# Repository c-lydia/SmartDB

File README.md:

# SmartDB

SmartDB is a household electrical fault detection and protection system spanning ESP32
firmware, KiCad hardware, a device-ingestion gateway, API examples, and engineering
reference material.

## Project links

| Project | Hosted website | GitHub | Role |
|---|---|---|---|
| SmartDB | [Documentation](https://smartdb-docs.vercel.app) | [c-lydia/SmartDB](https://github.com/c-lydia/SmartDB) | Hardware, firmware, backend/API and engineering documentation |
| SmartDB documentation | [Current architecture](https://smartdb-docs.vercel.app/system/architecture.html) · [PCB downloads](https://smartdb-docs.vercel.app/hardware/index.html#files-and-previews) · [API/team handoff](https://smartdb-docs.vercel.app/system/index.html) | [Documentation sources](https://github.com/c-lydia/SmartDB/tree/main/docs) | Public documentation site |
| ByteLab | [ByteLab Web](https://bytelab-web.vercel.app) | [c-lydia/ByteLab](https://github.com/c-lydia/ByteLab) | Related firmware development workspace; desktop and browser editions |
| SmartDB user dashboard | Not published yet | Repository not available yet | Owned by the frontend team; links will be added when available |

ByteLab is a development companion, not SmartDB's user dashboard. The optional local
SmartDB developer console is for API testing and is not publicly deployed.

## Repository map

| Path | Contents |
|---|---|
| [`backend/`](backend/) | Python CoAP/CBOR ingestion gateway and tests |
| [`cloud/`](cloud/README.md) | Implemented Firebase HTTP API, emulator launcher and frontend integration guide |
| [`dashboard/`](dashboard/README.md) | Optional developer console; user dashboard belongs to the frontend team |
| [`esp_idf/smartdb_fusion/`](esp_idf/smartdb_fusion/README.md) | PlatformIO ESP-IDF v2 system firmware and separate ESP32-CAM firmware; build/flash guide |
| [`smart_db/`](smart_db/smart_db.kicad_pro) | Earlier KiCad design and historical manufacturing outputs |
| [`smart_db_v2/`](smart_db_v2/README.md) | Selected hardware revision; review findings and ESP32-S3 module decision |
| [`postman/`](postman/documents/README.md) | User-facing HTTP API requests, OpenAPI contract, and collection guide |
| [`docs/`](docs/) | System architecture and engineering references |

## Run the backend locally

Run `sh system.sh` from this folder (Node.js 22 LTS and Java 21+ required). It starts
Firebase emulators and the optional developer console, prints a local administrator login,
and preserves local data on clean shutdown. The API is at `http://127.0.0.1:5000/api/v1`.
See the [team API handoff](cloud/README.md) for integration, Postman, device provisioning,
configuration commands and deployment. The frontend team owns the user dashboard.

## Set up the two boards

The [web documentation source](docs/index.md) includes the setup guide, hardware notes,
API guide and architecture. Rebuild it with `./docs/build.sh` and open
`docs/_build/html/index.html`; see [website maintenance](docs/README.md).

Open `esp_idf/smartdb_fusion` as the VS Code project folder, then choose
**Terminal → Run Task → SmartDB: Setup**. Alternatively, launch the menu from that folder:

```sh
./setup.sh
```

Choose **1** to enter Wi-Fi settings, **2** to set up the ESP32-CAM, then **3** to set up
the SmartDB main board. The menu selects ports, offers the initial firmware flash, saves
settings and checks Wi-Fi. Use **4** for protection limits. Later connection changes are
saved over USB without rebuilding. The camera and main board each need their own firmware;
PlatformIO combines their source files automatically.

Connect each board directly to the computer for setup. The main board's J6 camera socket
supplies power only and cannot program the camera. See the [firmware guide](esp_idf/smartdb_fusion/README.md)
for connections, configuration, recovery and calibration. The [full architecture](docs/architecture_full_v1.1.md)
separates implemented bench behavior from production requirements; the [backend guide](backend/README.md)
covers the separate CoAP ingestion gateway.

## Current hardware

SmartDB v2 is being corrected for an ESP32-S3-WROOM-1-N16R8 module supplied and assembled
by JLCPCB. The existing ESP32-WROOM-32 development board is separate test hardware, not
the selected PCB module. The module replacement is applied in the KiCad
schematic and PCB, with corrected reset/boot wiring and an updated [pin map](smart_db_v2/pinmap.csv).
The current revision targets a **low-voltage bench load**, with corrected 5 V logic power,
USB, CT input and a separate normally-open relay contact connector. The permanent
[v2 project](smart_db_v2/smart_db/smart_db.kicad_pro) now contains the 95 × 78 mm
compact redesign with an AP63203 buck supply, four copper layers, and the SmartDB
logo and connector labels. All PCB connections are routed, with wider signal and power
traces and continuous inner ground planes. ERC, DRC, connectivity and schematic parity
checks report zero issues. See the [v2 review](smart_db_v2/README.md) for current validation results,
previews and the archived previous board. It is not a mains protection board.

## Project maturity

The v2 bench firmware now covers SCT-013 **isolated low-voltage AC** monitoring, MLX90640
thermal sensing, local relay protection with physical re-arm, persistent configuration/events,
registered RGB–thermal fusion and optional HTTPS diagnostic telemetry using the Postman
contract. Build `smartdb_s3` for the main board and `esp32cam` for the separate camera.
See the [firmware guide](esp_idf/smartdb_fusion/README.md) for configuration, flashing,
calibration and implementation limits. Source/build verification is complete; physical bench
validation remains pending. The PCB logic supply is DC; the CT measurement is AC-only.

This is an engineering-stage repository, not a production-certified safety device. The
backend's secure transport integration and several firmware/hardware validation activities
remain explicit pre-production work. Do not use it as the sole protective mechanism for a
live electrical installation.

## Code style

Maintained application code uses two-space indentation for JavaScript, CSS, and shell,
four spaces for Python and C, and a 100-column target. Prettier handles the web/API code,
Ruff formats and checks Python, clang-format handles the current firmware, and shfmt
formats shell scripts. Editor defaults are in `.editorconfig`.

C code uses an open, Python-like layout: one statement per line, spaces around operators,
braced control-flow blocks, and blank lines between functions and logical steps.

Install the development tools with `npm ci` and, inside a Python virtual environment,
`python -m pip install -r requirements-dev.txt`. Install clang-format and shfmt separately;
the formatting baseline uses clang-format 23.1.0 and shfmt 3.13.1.

```sh
npm run format        # Apply formatting
npm run format:check  # Check formatting and Python imports/errors without rewriting files
npm run build        # Build the developer console
npm test             # Run the cloud API tests using local Firebase emulators
python -m pytest backend/tests
sh esp_idf/smartdb_fusion/tools/check.sh
```

The formatting commands cover `backend`, `cloud`, `dashboard`, documentation support
scripts/styles, launchers, and first-party code in `esp_idf/smartdb_fusion`. They exclude
generated outputs, local firmware configuration, upstream sensor drivers, legacy firmware
examples, hardware design files, archives, and Postman exports.

## Related projects

- [ByteLab](https://github.com/c-lydia/ByteLab) — firmware development workspace; [hosted browser edition](https://bytelab-web.vercel.app) and [SmartDB integration guide](https://smartdb-docs.vercel.app/related/bytelab.html).

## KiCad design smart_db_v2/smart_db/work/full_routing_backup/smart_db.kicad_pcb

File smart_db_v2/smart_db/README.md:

# SmartDB compact redesign — board routing complete

Updated 2026-10-10. **Fully routed bench prototype; fabrication review remains.**

Open [smart_db.kicad_pro](smart_db.kicad_pro) in KiCad. The editable
[schematic](smart_db.kicad_sch), [PCB](smart_db.kicad_pcb), project-local symbol and
footprint libraries are saved together here. This is the permanent v2 project,
moved from `../compact_wip/`. The previous routed bench revision and its reports
are preserved in [the archive](../archive/bench_before_compact_2026-10-08/README.md).

## Saved work

- Draft 95 × 78 mm four-layer placement, outward-facing connectors and four M3
  mounting holes with screw-head copper clearances.
- Revised AP63203 buck supply, bulk/local decoupling, ADC supply filter and test points.
- Schematic organized into six numbered subsystem boxes.
- Monochrome vector logo extracted from the cover of
  `formal_docs/proposal/SmartDB_proposal_final.pdf`, saved as
  [work/smartdb-logo-monochrome.svg](work/smartdb-logo-monochrome.svg).
  The logo is now on the front silkscreen, together with functional connector,
  BOOT/RESET, status and power labels. The back has connector pin and polarity labels.
- Corrected overlaps involving the relay flyback diode, MCU reset capacitor/pullup,
  ADC decoupling and relay-coil decoupling. The local ESP32 footprint now matches
  the board, including its four-layer antenna keepout and edge silkscreen treatment.

## Connector access and routing

Working board construction: **four-layer FR-4, 1.6 mm overall thickness,
1 oz outer copper and 0.5 oz inner copper**, following the request for standard
construction. The layer order is signal/power–ground–ground–signal/power.
Manufacturer-specific dielectric spacing remains to be selected.

- J3 is the four-pin I²C header. Its pins now project approximately 5.5 mm past
  the left board edge. Front and back labels identify **1 SDA, 2 SCL, 3 GND, 4 3V3**.
  J2 remains the two-pin regulated 5 V screw terminal.
- J4 moved 7.64 mm toward the left edge. Its original mid-mount cutout is retained;
  the unnecessary additional recess is removed. D7 moved 6 mm toward the connector.
- All nets are routed, including buck supply, relay/load, ADC, I²C, UART, USB,
  reset/boot, LEDs and buzzer. Signals remain on F.Cu and B.Cu; both inner layers
  remain ground planes. Final copper contains 608 segments and 88 vias.
- The buck switch and bootstrap connections are short front-layer routes. The
  output has a wider distribution path and separate feedback branch. Load contacts
  use 1 mm traces without vias. Ground stitches connect the ADC, input protection,
  decoupling and MCU regions to the inner planes.
- R13 moved to (73, 70) mm to open a clean reset/enable routing path.
- The USB main pair is manually routed, with 0.2 mm traces, 0.3 mm gap and two
  layer transitions per main path. Preferred widths are now 0.30 mm for signals,
  0.60 mm for power, 0.75 mm for the 5 V/coil supply and 1.00 mm for load contacts.
  Actual routing retains narrower sections in congested channels and pad escapes;
  the minimum is 0.20 mm. USB dimensions were preserved.
- USB appearance now uses a **simplified local visualization**, clearly identified
  in `SmartDB.3dshapes/`. The manufacturer STEP download returned HTTP 403, and
  KiCad's referenced model was unavailable. This is not an enclosure-fit model.

## STEP export

[smart_db.step](smart_db.step) now exports successfully with all three previously
problematic parts included. D6, J1 and J4 reference project-local STEP files through
`${KIPRJMOD}`. J1 uses the [official Same Sky model](https://www.sameskydevices.com/product/resource/3dmodel/sj-3523-smt-tr),
aligned to the footprint. D6 uses a simplified 3.5 × 2.8 × 0.6 mm package preview
based on [ROHM's drawing, page 263](https://fscdn.rohm.com/en/products/databook/catalog/common/shortform2023/SF2023_EN_P247_LEDs.pdf).
J4 uses a STEP solid version of the existing simplified USB preview. D6 and J4
are visual approximations, not certified enclosure-fit models.

Model sources and transforms are recorded in `SmartDB.3dshapes/provenance.json`.
The model fix preserves all copper, pads, placements and rules. Its original CAD
and incomplete STEP are preserved in `work/before_step_model_fix/`.
Reopen the PCB from disk before exporting in an already-open KiCad window;
an old editor buffer still contains the previous model references.

## Two-camera connections

- **J3:** MLX90640 thermal camera, 1 SDA / 2 SCL / 3 GND / 4 3V3.
- **J6:** USB-A **5 V camera power output**, using a
  [TE 292303-7](https://www.te.com/en/product-292303-7.html) socket with SMD
  contacts and two through-hole shell anchors. Connect a short **USB-A to
  micro-USB cable** to the external ESP32-CAM-MB base shown in the reference photo.
  USB pin 1 is +5V, pin 4 and the shell are ground; pins 2 and 3 are intentionally
  unconnected. This is a dedicated camera power connection, with no USB host,
  data, programming or charging-port negotiation on J6.

J6 is at the bottom edge, at (103, 117.3) mm. It branches from F1's
protected output, with a 1.0 mm main trace on B.Cu, a 0.75 mm fuse-pad connection
and paired 0.8/0.4 mm vias at both ends. A 0.75 mm front-layer connection reaches
VBUS without crossing the existing 3.3 V route. C25 (10 µF, 16 V, X7R, 0805) and
C26 (100 nF, 16 V, X7R, 0603) provide local bypassing near J6; capacitor and
connector ground vias join the internal planes. All pre-camera routes and
placements are preserved. The logo was reduced and moved left for clearance.
The local USB-A footprint only moves the three edge-clipped silkscreen segments
to F.Fab; contact pads and the KiCad STEP model are unchanged. TE recommends
1.42 mm PCB thickness for this connector; verify shell retention and soldering
with actual parts on the project's 1.6 mm PCB before fabrication release.
F1's symbol now correctly identifies its specified part as a
one-time fast-acting fuse, rather than a resettable device.

Wi-Fi is the image-data path. The current [PlatformIO ESP-IDF firmware](../../esp_idf/smartdb_fusion/README.md)
has an `esp32cam` target serving authenticated fresh QVGA JPEGs at `/capture`, and a
`smartdb_s3` target combining those images with MLX90640 data. This is request-driven
capture, not a USB video stream. Real alignment and capture timing still need hardware validation.
The older SD-card diagnostic camera project remains separate.

Run the firmware project's `./setup.sh` menu or its **SmartDB: Setup** VS Code task to
install/configure each board. Program the camera by connecting its base directly to the
computer; J6 cannot program it. Configure the camera first so the menu can supply its Wi-Fi
address to the S3. Subsequent Wi-Fi/token/endpoint changes persist in NVS without reflashing;
protection limits are also configurable through the menu, with physical re-arm still required.

Supply both boards through J2 from regulated 5 V; a 2 A capable source is a
provisional supply target. J4 USB-C remains the data/programming connection;
J6 USB-A supplies camera power. The shared 1.5 A F1 is not
an independent camera current limiter. Reserve 0.5 A for the camera/base and target
no more than 1.1 A combined continuous input at 25°C; this is a design budget,
not a measured current rating. Temperature derating, simultaneous Wi-Fi bursts,
camera flash/SD activity, startup and cable voltage drop still need validation.
See [power review and sources](work/camera_power_review.json). The pre-addition
CAD and reports are preserved in `work/before_camera_power/`; the preceding
JST camera-power revision is preserved in `work/before_camera_usb/`.

See [routing review](work/routing_review.md), [copper PDF](work/routing_current.pdf)
and [3D preview](work/connectors_current.png). Existing placement, schematic and
label previews below have also been regenerated.

## Validation status and remaining work

Current KiCad 10.0.6 results: **ERC 0 violations; PCB DRC 0 geometric/library/silkscreen
violations, 0 unconnected items, 0 schematic/PCB mismatches.**
No clearance rules, DRC severities or exclusions were changed. Default and Power
preferred widths changed to 0.30 and 0.60 mm at the user’s request. The resume baseline had 22 placement
violations (including three pad shorts), 113 unconnected items and no parity issues.

Current review outputs:

- [Placement PDF](work/placement_current.pdf) / [PNG](work/placement_current.png)
- [Bottom labels PDF](work/back_labels_current.pdf) / [PNG](work/back_labels_current.png)
- [Schematic PDF](work/schematic_current.pdf) and [netlist](work/netlist_current.xml)
- [ERC](work/erc_current.json), [DRC](work/drc_routing_current.json), and
  [source hashes and checks](work/validation_current.json)

Files without the `current` suffix remain historical intermediate outputs.
`work/resume_backup/` preserves the board, schematic, project and local footprint
as they were at the start of this continuation. `SNAPSHOT.json` describes the
original paused snapshot; it is not the hash manifest for today's revised sources.

Routing is complete. USB impedance and timing still need manufacturer stackup
review and measurement. The selected 1 oz construction does not qualify the
buck circuit for its IC’s maximum 2 A rating; current and thermal limits require review.
Check connector access, mounting clearances, capacitor placement, current paths,
voltage drop, USB geometry, antenna clearance and silkscreen. Recheck labels after
routing and regenerate the review outputs. Verify the exact supply, component selections
and capacitor derating before fabrication. Hardware load-step, brownout, relay,
thermal, USB and ADC-noise measurements remain necessary; a rule-check pass cannot
establish that assembled hardware works.

No enclosure dimensions or J2 supply model have been confirmed.
The design remains scoped to a regulated 5 V supply and a provisional 5–24 V DC,
up-to-1 A resistive relay test load. No mains use.

## Resuming the editing scripts

`work/` preserves the staging scripts and evidence; `work/helpers/` preserves
helpers they import. They contain original absolute `/tmp/smartdb_review/...`
paths and some rebuild earlier stages. **Do not run them blindly against this
snapshot.** Restore the original staging structure or review/update paths first.
The files at this snapshot's root are the authoritative saved CAD state.
`SNAPSHOT.json` records the original paths and hashes of all copied files.

The new `work/resume_placement.py` and `work/add_board_labels.py` resolve paths
relative to this project. The first requires KiCad's Python runtime and refuses
to move components once tracks/vias exist; the second uses ordinary Python and
replaces only its own deterministically identified graphics. In this environment:

```sh
flatpak run --command=python3 org.kicad.KiCad work/resume_placement.py
python3 work/add_board_labels.py
```

These are placement-stage tools. Do not replay placement after hand edits without
reviewing its explicit coordinates. Use `work/validate_current.py` after generating
fresh ERC, DRC and netlist outputs to refresh the source-hash/check manifest.

The connector/routing scripts added in this session are preserved as engineering
work records, not a one-command rebuild pipeline. Some restore earlier board
stages or append copper. **Do not replay them on the current routed board.**
The root CAD files and `work/validation_current.json` are authoritative. The
older `drc_placement_current.json` describes the placement-only milestone.

`work/routed_checkpoint/` preserves the completed CAD and final DRC report.
`work/full_routing_backup/` preserves the earlier partially routed state.
An older editor copy saved during routing is preserved separately in
`work/editor_saved_during_routing.kicad_pcb`. Reopen the project before editing
so an old editor buffer does not overwrite the completed routes.

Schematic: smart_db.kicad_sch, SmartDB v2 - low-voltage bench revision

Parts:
BZ1: Buzzer (3V3 type TBD); Buzzer_12x9.5RM7.6
C1: 220nF; C_0805_2012Metric_Pad1.18x1.45mm_HandSolder
C2, C9: 10uF; C_0805_2012Metric_Pad1.18x1.45mm_HandSolder
C3, C10: 100nF; C_0805_2012Metric_Pad1.18x1.45mm_HandSolder
C4: 10uF 10V X7R; C_0805_2012Metric
C5: 10uF 10V X7R; C_1206_3216Metric
C6, C20: 100nF 10V X7R; C_0805_2012Metric_Pad1.18x1.45mm_HandSolder
C7, C8, C23: 22uF 10V X7R; C_1206_3216Metric
C11: 1uF; C_0805_2012Metric_Pad1.18x1.45mm_HandSolder
C15, C18: 100nF; C_0603_1608Metric
C16, C17: 4.7uF; C_0805_2012Metric_Pad1.18x1.45mm_HandSolder
C19: 10uF 10V X7R; C_0805_2012Metric_Pad1.18x1.45mm_HandSolder
C21: 100nF 25V X7R; C_0603_1608Metric
C22, C24: 100uF 10V; CP_Elec_6.3x7.7
D1: M7 (1N4007 SMD); D_SMA
D2: ADC POWER; LED_0805_2012Metric_Pad1.15x1.40mm_HandSolder
D5: POWER; LED_0805_2012Metric_Pad1.15x1.40mm_HandSolder
D6: SMLVN6RGB1U1; LED_ROHM_SMLVN6
D7: SP0503BAHTG; SOT-143
D8: USB BRIDGE POWER; LED_0805_2012Metric_Pad1.15x1.40mm_HandSolder
D9, D10: BAT54S; SOT-23
F1: 046701.5NRHF 1.5A; Fuse_0603_1608Metric
H1, H2, H3, H4: M3 mounting; MountingHole_3.2mm_M3
J1: SCT-013-000 ONLY; Jack_3.5mm_CUI_SJ-3523-SMT_Horizontal
J2: REGULATED 5V INPUT; TerminalBlock_Phoenix_MKDS-1,5-2_1x02_P5.00mm_Horizontal
J3: THERMAL_I2C; PinHeader_1x04_P2.54mm_Horizontal_Edge
J4: USB_C_Receptacle_USB2.0_14P; USB_C_Receptacle_Amphenol_12401948E412A_Preview
J5: TEST_LOAD; TerminalBlock_Phoenix_MKDS-1,5-2_1x02_P5.00mm_Horizontal
K1: G5LE-1 DC5; Relay_SPDT_Omron-G5LE-1
L1: 6.8uH SRP5030TA-6R8M; L_Bourns_SRP5030T
Q1, Q2: AO3400A; SOT-23
R1, R2: 1k 1%; R_0805_2012Metric_Pad1.20x1.40mm_HandSolder
R3, R4: 10k 1%; R_0805_2012Metric_Pad1.20x1.40mm_HandSolder
R6, R15: 100; R_0805_2012Metric_Pad1.20x1.40mm_HandSolder
R7, R8: 4.7k; R_0805_2012Metric_Pad1.20x1.40mm_HandSolder
R9, R21: 1k; R_0805_2012Metric_Pad1.20x1.40mm_HandSolder
R12, R16, R17, R18, R22: 330; R_0805_2012Metric_Pad1.20x1.40mm_HandSolder
R13, R14: 10k; R_0805_2012Metric_Pad1.20x1.40mm_HandSolder
R19: 22.1k; R_0805_2012Metric_Pad1.20x1.40mm_HandSolder
R20: 47.5k; R_0805_2012Metric_Pad1.20x1.40mm_HandSolder
R23: 18 ohm 1% 0.25W; R_0805_2012Metric_Pad1.20x1.40mm_HandSolder
R24, R25: 5.1k; R_0805_2012Metric_Pad1.20x1.40mm_HandSolder
R26, R27, R28: 100k; R_0805_2012Metric_Pad1.20x1.40mm_HandSolder
R29: 0R 1A min; R_0805_2012Metric
R30: 10R 1%; R_0603_1608Metric
SW2: BOOT; SW_Push_1P1T_NO_CK_KMR2
SW3: RESET; SW_Push_1P1T_NO_CK_KMR2
TP1: LOGIC_5V_FUSED; TestPoint_Pad_D1.5mm
TP2: VCC; TestPoint_Pad_D1.5mm
TP3: MCU_3V3; TestPoint_Pad_D1.5mm
TP4: ADC_3V3; TestPoint_Pad_D1.5mm
TP5: BGND; TestPoint_Pad_D1.5mm
U1: ADS1115IDGS; TSSOP-10_3x3mm_P0.5mm
U3: AP63203WU-7; TSOT-23-6
U4: ESP32-S3-WROOM-1-N16R8; ESP32_S3_WROOM_1_Edge; JLCPCB Part C2913202
U5: CP2102N-A02-GQFN28; QFN-28-1EP_5x5mm_P0.5mm_EP3.35x3.35mm

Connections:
ADC_3V3: C3.1, C4.1, D9.2 (K), D10.2 (K), R3.1, R30.2, TP4.1 (1_1), U1.8 (VDD)
ADC_AIN0: C1.1, D9.3 (COM), R1.2, U1.4 (AIN0)
ADC_AIN1: C1.2, D10.3 (COM), R2.2, U1.5 (AIN1)
ADC_LED_A: D2.2 (A), R9.2
BGND: C2.2, C3.2, C4.2, C5.2, C6.2, C7.2, C8.2, C9.2, C10.2, C11.2, C15.2, C16.2, C17.2, C18.2, C19.2, C20.2, C22.2, C23.2, C24.2, D2.1 (K), D5.1 (K), D6.4 (GK), D6.5 (RK), D6.6 (BK), D7.1 (A), D8.1 (K), D9.1 (A), D10.1 (A), J2.1, J3.3, J4.A1 (GND), J4.A12 (GND), J4.B1 (GND), J4.B12 (GND), J4.SH (SHIELD), Q1.2 (S), Q2.2 (S), R4.2, R20.2, R24.2, R25.2, R26.2, R27.2, R28.2, SW2.1, SW3.1, TP5.1 (1_1), U1.1 (ADDR), U1.3 (GND), U1.6 (AIN2), U1.7 (AIN3), U3.4 (GND), U4.1 (GND), U4.40 (GND), U4.41 (GND), U5.3 (GND), U5.29 (GND)
BOOT: R14.2, SW2.2, U4.27 (IO0)
BUCK_BST: C21.1, U3.6 (BST)
BUCK_SW: C21.2, L1.1, U3.5 (SW)
BUZZER_DRIVE: R15.1, U4.5 (IO5)
BUZZER_LOW: BZ1.2 (-), Q2.3 (D)
CTL: R6.1, R27.1, U4.4 (IO4)
CT_BIAS: C2.1, J1.S, R2.1, R3.2, R4.1, R23.2
CT_HI: J1.T, R1.1, R23.1
EN: C11.1, R13.2, SW3.2, U4.3 (EN)
LED_B: R18.1, U4.12 (IO8)
LED_B_A: D6.1 (BA), R18.2
LED_G: R17.1, U4.7 (IO7)
LED_G_A: D6.3 (GA), R17.2
LED_R: R16.1, U4.6 (IO6)
LED_R_A: D6.2 (RA), R16.2
LOAD_IN: J5.1, K1.1
LOAD_OUT: J5.2, K1.3
LOGIC_5V_FUSED: C5.1, C6.1, C19.1, C20.1, C22.1, C24.1, D1.1 (K), F1.2, K1.5, TP1.1 (1_1), U3.2 (EN), U3.3 (IN)
LOGIC_5V_IN: F1.1, J2.2
MCU_3V3: BZ1.1 (+), C9.1, C10.1, C23.1, J3.4, R7.1, R8.1, R12.1, R13.1, R14.1, R29.2, TP3.1 (1_1), U4.2 (3V3)
unnamed: D5.2 (A), R12.2
unnamed: Q2.1 (G), R15.2, R26.1
RELAY_GATE: Q1.1 (G), R6.2, R28.1
RELAY_LOW: D1.2 (A), K1.2, Q1.3 (D)
RX: U4.37 (TXD0), U5.25 (RXD)
SCL: J3.2, R7.2, U1.10 (SCL), U4.38 (IO2)
SDA: J3.1, R8.2, U1.9 (SDA), U4.18 (IO10)
TX: U4.36 (RXD0), U5.26 (TXD)
USB_CC1: J4.A5 (CC1), R24.1
USB_CC2: J4.B5 (CC2), R25.1
USB_D+: D7.2 (K), J4.A6 (D+), J4.B6 (D+), U5.4 (D+)
USB_D-: D7.3 (K), J4.A7 (D-), J4.B7 (D-), U5.5 (D-)
USB_LED_A: D8.2 (A), R22.2
USB_RESET: R21.2, U5.9 (~RST)
USB_VBUS: D7.4 (K), J4.A4 (VBUS), J4.A9 (VBUS), J4.B4 (VBUS), J4.B9 (VBUS), R19.1
USB_VBUS_SENSE: R19.2, R20.1, U5.8 (VBUS)
VCC: C7.1, C8.1, C15.1, C16.1, C17.1, C18.1, L1.2, R9.1, R21.1, R22.1, R29.1, R30.1, TP2.1 (1_1), U3.1 (FB), U5.6 (VDD), U5.7 (VREGIN)

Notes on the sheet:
01 POWER / 5 V TO 3.3 V
J2 regulated 5 V only. Buck + local reservoirs. Not battery charging.
02 USB / UART PROGRAMMING
USB is data only; J2 powers the board. Hold BOOT, pulse RESET.
03 ESP32-S3 / BOOT / RESET
ESP32-S3-WROOM-1-N16R8. Module RF keepout on every copper layer.
04 CT / ADC ANALOG FRONT END
AC current transformer only. Differential AIN0-AIN1, address 0x48.
05 RELAY / TEST LOAD
Normally-open dry contact loop. 5-24 V DC / 1 A resistive bench target.
06 INDICATORS / EXTERNAL I2C
3.3 V logic only. Buzzer part selection and bench measurements pending.
MECHANICAL + MEASUREMENT POINTS

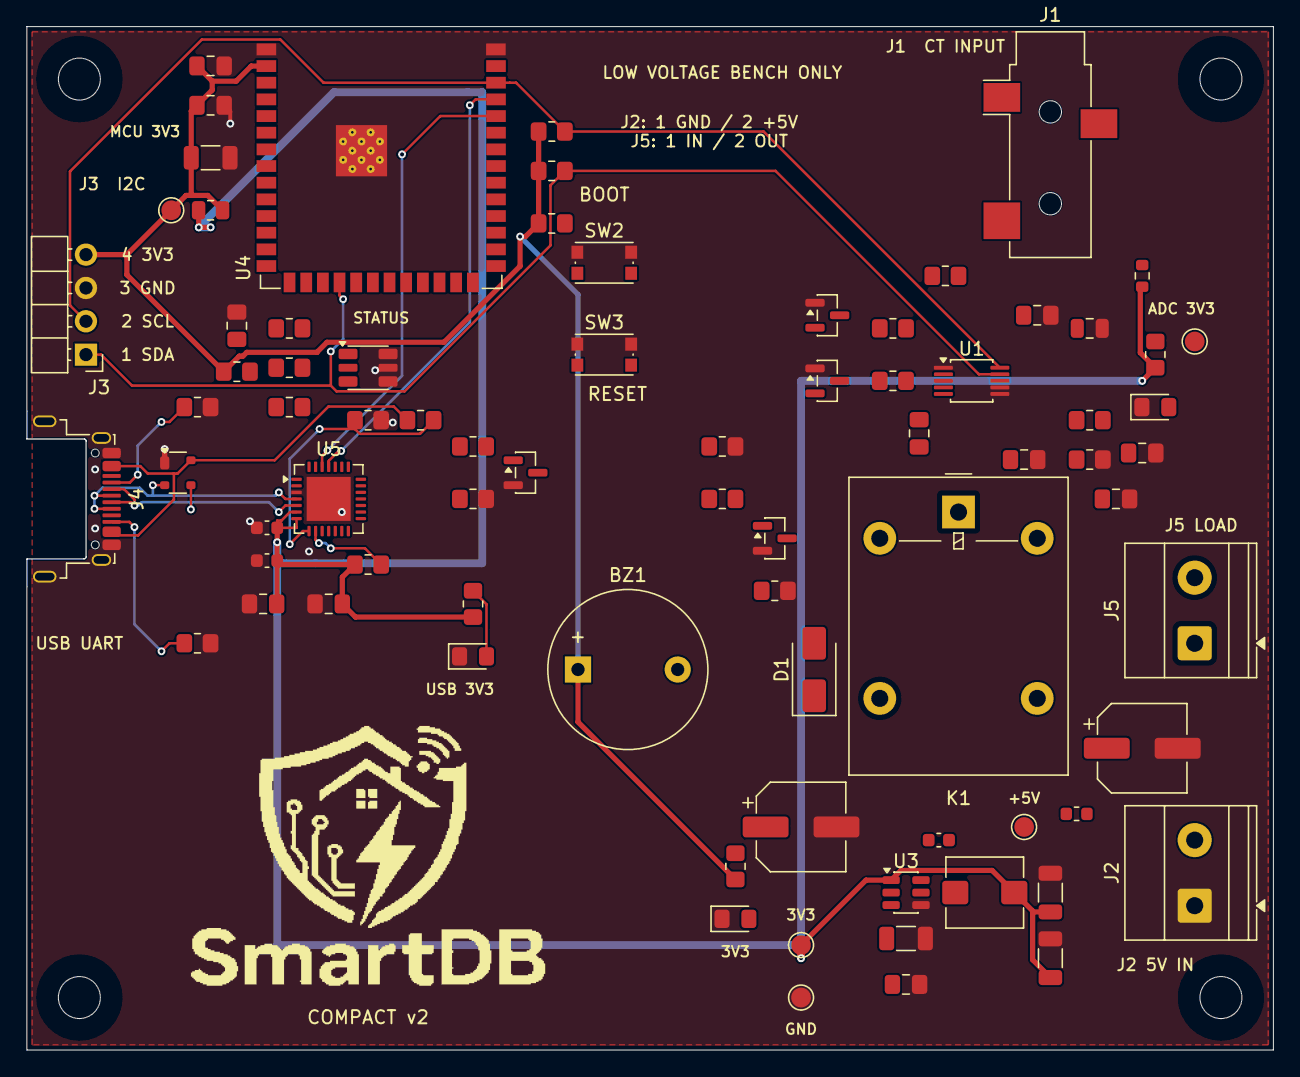
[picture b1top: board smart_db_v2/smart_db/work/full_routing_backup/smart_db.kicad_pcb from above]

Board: 4 copper layers, 95.0 x 78.0 mm, 82 parts (0 on the bottom side), 42 nets.

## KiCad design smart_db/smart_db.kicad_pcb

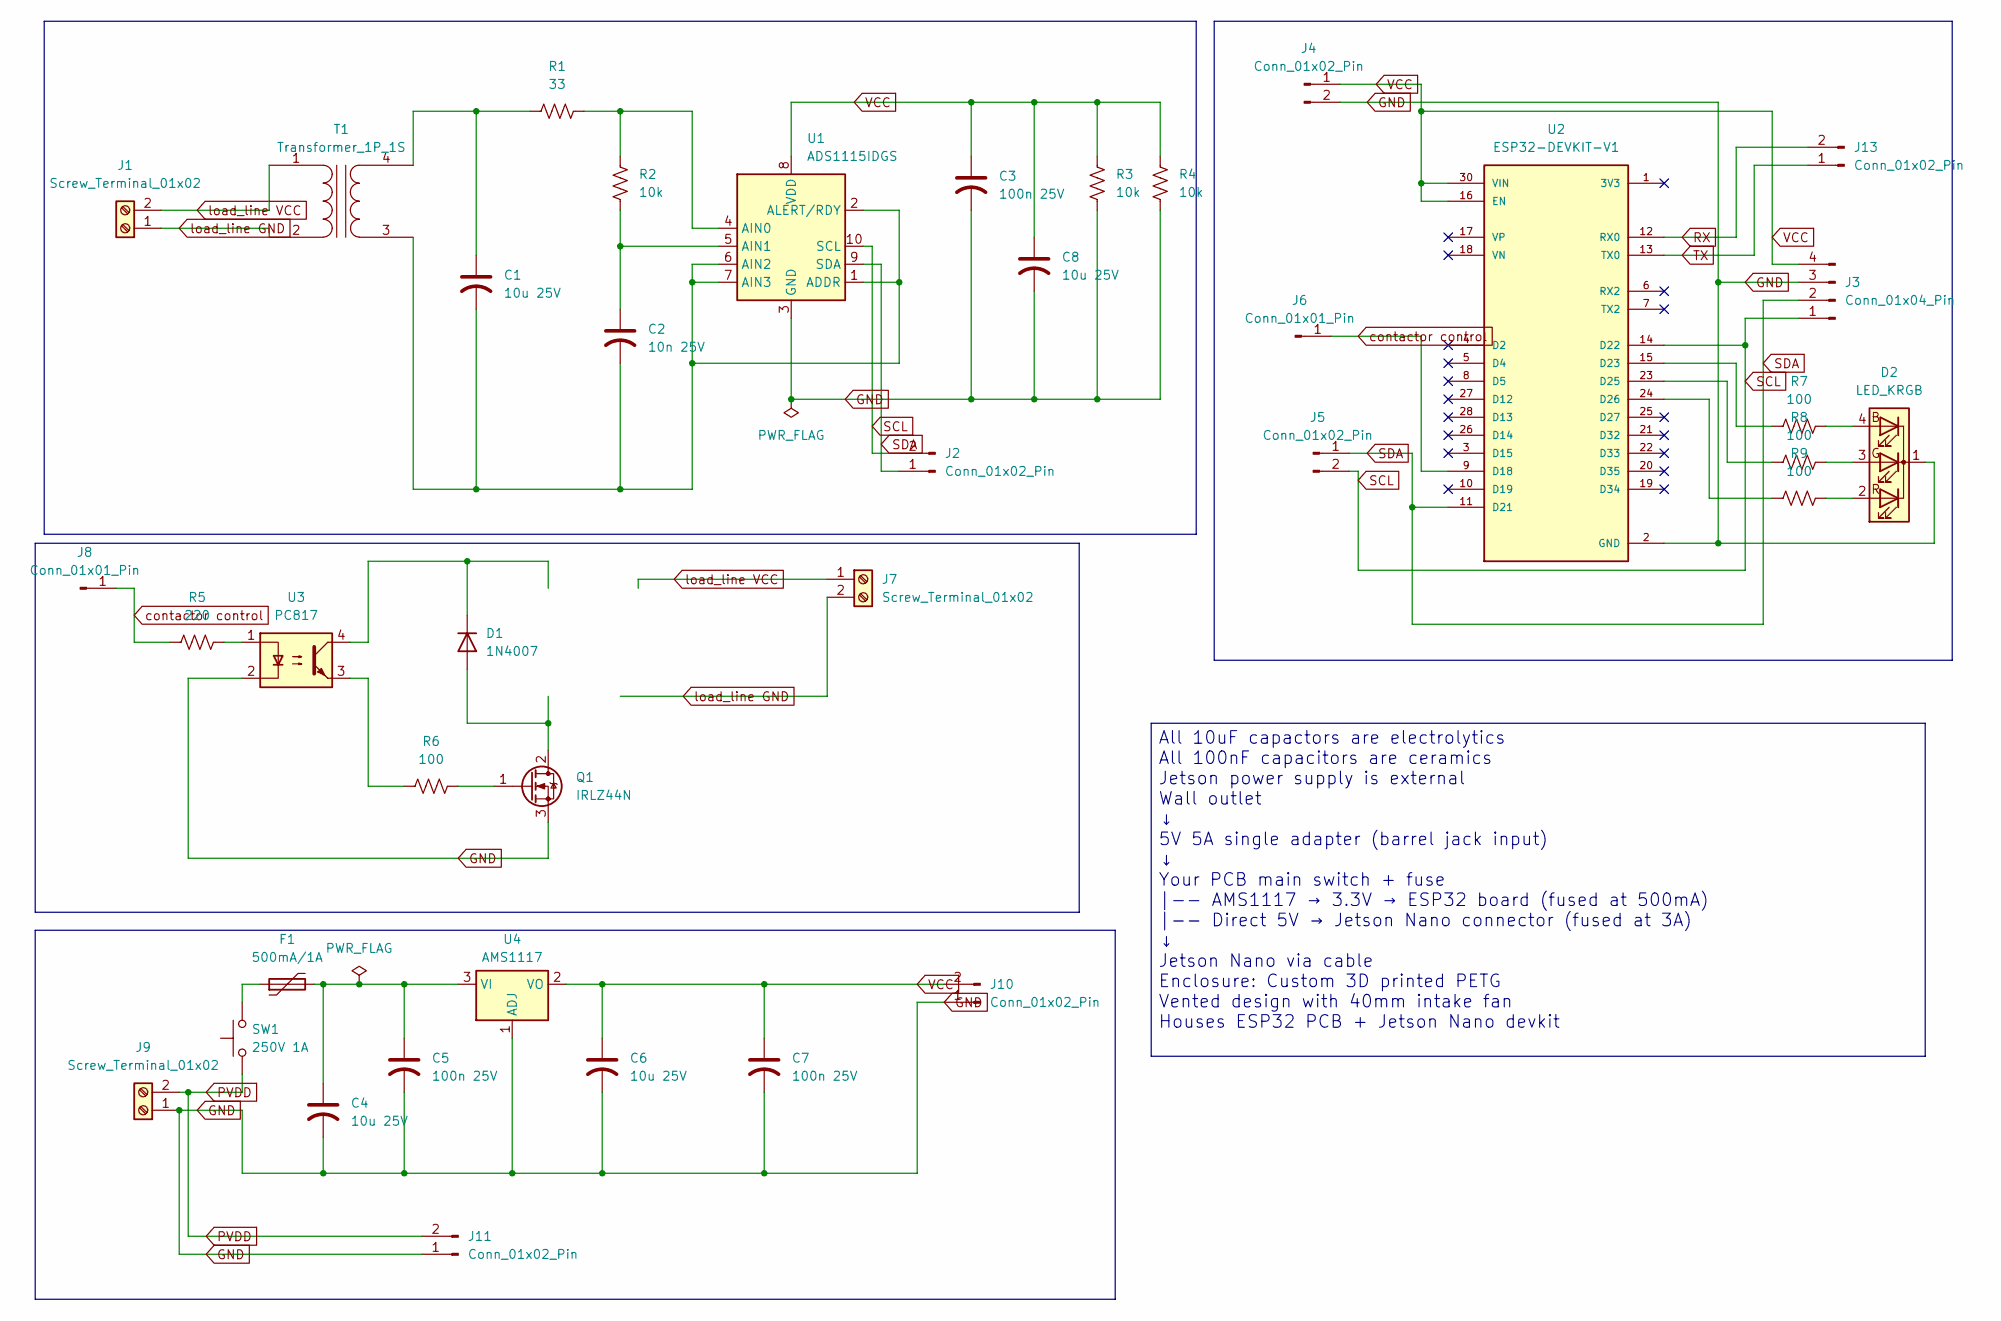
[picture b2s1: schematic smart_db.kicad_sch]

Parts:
C1, C4, C6, C8: 10u 25V; CP_Radial_D5.0mm_P2.50mm
C2: 10n 25V; C_Disc_D3.0mm_W1.6mm_P2.50mm
C3, C5, C7: 100n 25V; C_Disc_D3.0mm_W1.6mm_P2.50mm
D1: 1N4007; D_DO-41_SOD81_P10.16mm_Horizontal
D2: LED_KRGB; LED_D5.0mm-4_RGB
F1: 500mA/1A; Fuse_Bourns_MF-RHT050
J1, J7, J9: Screw_Terminal_01x02; TerminalBlock_RND_205-00276_1x02_P5.00mm_Vertical
J2, J4, J5, J10, J11, J13: Conn_01x02_Pin; PinHeader_1x02_P2.54mm_Vertical
J3: Conn_01x04_Pin; PinHeader_1x04_P2.54mm_Vertical
J6, J8: Conn_01x01_Pin; PinHeader_1x01_P2.54mm_Vertical
Q1: IRLZ44N; TO-220-3_Vertical
R1: 33; R_Axial_DIN0207_L6.3mm_D2.5mm_P10.16mm_Horizontal
R2, R3, R4: 10k; R_Axial_DIN0204_L3.6mm_D1.6mm_P7.62mm_Horizontal
R5: 220; R_Axial_DIN0204_L3.6mm_D1.6mm_P2.54mm_Vertical
R6: 100; R_Axial_DIN0204_L3.6mm_D1.6mm_P2.54mm_Vertical
R7, R8, R9: 100; R_Axial_DIN0204_L3.6mm_D1.6mm_P7.62mm_Horizontal
SW1: 250V 1A; SW_PUSH_1P1T_6x3.5mm_H5.0_APEM_MJTP1250
T1: Transformer_1P_1S; TerminalBlock_RND_205-00278_1x04_P5.00mm_Vertical
U1: ADS1115IDGS; TSSOP-10_3x3mm_P0.5mm
U2: ESP32-DEVKIT-V1; MODULE_ESP32_DEVKIT_V1; PARTREV N/A
U3: PC817; DIP-4_W7.62mm
U4: AMS1117; SOT-223-3_TabPin2

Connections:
GND: C3.2, C4.2, C5.2, C6.2, C7.2, C8.2, D2.1 (K), J3.3, J4.2, J9.1, J10.1, J11.1, Q1.3 (S), R3.2, R4.2, U1.3 (GND), U2.2 (GND), U2.29 (GND), U3.2, U4.1 (ADJ); also elsewhere on the board
unnamed 1: D1.2 (A), Q1.2 (D); also elsewhere on the board
unnamed 2: D1.1 (K), U3.4; also elsewhere on the board
unnamed: D2.4 (BA), R7.2
unnamed: D2.3 (GA), R8.2
unnamed: D2.2 (RA), R9.2
unnamed: F1.1, SW1.2
unnamed: Q1.1 (G), R6.1
unnamed: R5.2, U3.1
unnamed: R6.2, U3.3
unnamed: C1.2, C2.2, T1.3 (SA), U1.1 (ADDR), U1.2 (ALERT/RDY), U1.6 (AIN2), U1.7 (AIN3)
unnamed: C1.1, R1.1, T1.4 (SB)
unnamed: R1.2, R2.1, U1.4 (AIN0)
unnamed: C2.1, R2.2, U1.5 (AIN1)
unnamed: R7.1, U2.15 (D23)
unnamed: R8.1, U2.23 (D25)
unnamed: R9.1, U2.24 (D26)
unnamed: C4.1, C5.1, F1.2, U4.3 (VI)
PVDD: J9.2, J11.2, SW1.1; also elsewhere on the board
RX: J13.2, U2.12 (RX0)
SCL: J2.2, J3.1, J5.2, U1.10 (SCL), U2.14 (D22)
SDA: J2.1, J3.2, J5.1, U1.9 (SDA), U2.11 (D21)
TX: J13.1, U2.13 (TX0)
VCC: C3.1, C6.1, C7.1, C8.1, J3.4, J4.1, J10.2, R3.1, R4.1, U1.8 (VDD), U2.16 (EN), U2.30 (VIN), U4.2 (VO)
contactor control: J6.1 (Pin_1_1), J8.1 (Pin_1_1), R5.1, U2.9 (D18)
load_line GND: J1.1, J7.2, T1.2 (AB); also elsewhere on the board
load_line VCC: J1.2, J7.1, T1.1 (AA); also elsewhere on the board

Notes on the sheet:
All 10uF capactors are electrolytics All 100nF capacitors are ceramics Jetson power supply is external Wall outlet ↓ 5V 5A single adapter (barrel jack input) ↓ Your PCB main switch + fuse |-- AMS1117 → 3.3V → ESP32 board (fused at 500mA) |-- Direct 5V → Jetson Nano connector (fused at 3A) ↓ Jetson 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

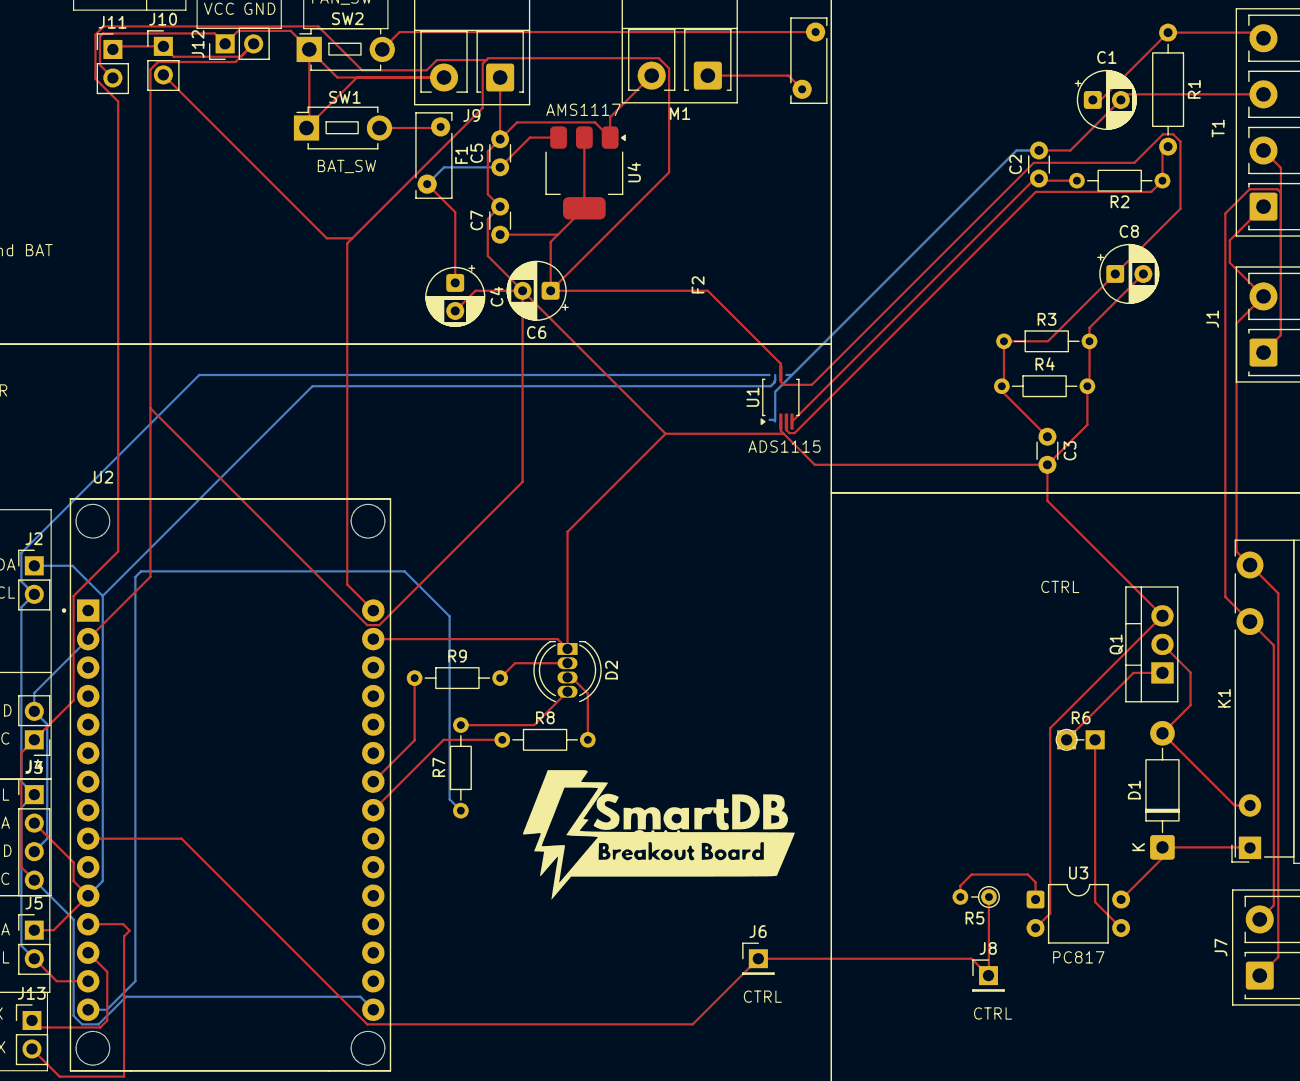
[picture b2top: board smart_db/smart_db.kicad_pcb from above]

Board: 2 copper layers, 44 parts (0 on the bottom side), 29 nets.

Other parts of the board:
F2: 200mA/400mA; Fuse_Bourns_MF-RHT050
J12: Conn_01x02_Pin; PinHeader_1x02_P2.54mm_Vertical
K1: Fujitsu_FTR-LYAA005x; Relay_SPST-NO_Fujitsu_FTR-LYAA005x_FormA_Vertical
M1: 5V 0.1A; TerminalBlock_RND_205-00276_1x02_P5.00mm_Vertical
SW2: 250V 1A; SW_PUSH_1P1T_6x3.5mm_H5.0_APEM_MJTP1250

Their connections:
GND: J12.2, M1.2 (-); also elsewhere on the board
unnamed 1: K1.A2; also elsewhere on the board
unnamed 2: K1.A1; also elsewhere on the board
unnamed: F2.2, SW2.2
unnamed: F2.1, M1.1 (+)
PVDD: J12.1, SW2.1; also elsewhere on the board
load_line GND: K1.13; also elsewhere on the board
load_line VCC: K1.14; also elsewhere on the board
